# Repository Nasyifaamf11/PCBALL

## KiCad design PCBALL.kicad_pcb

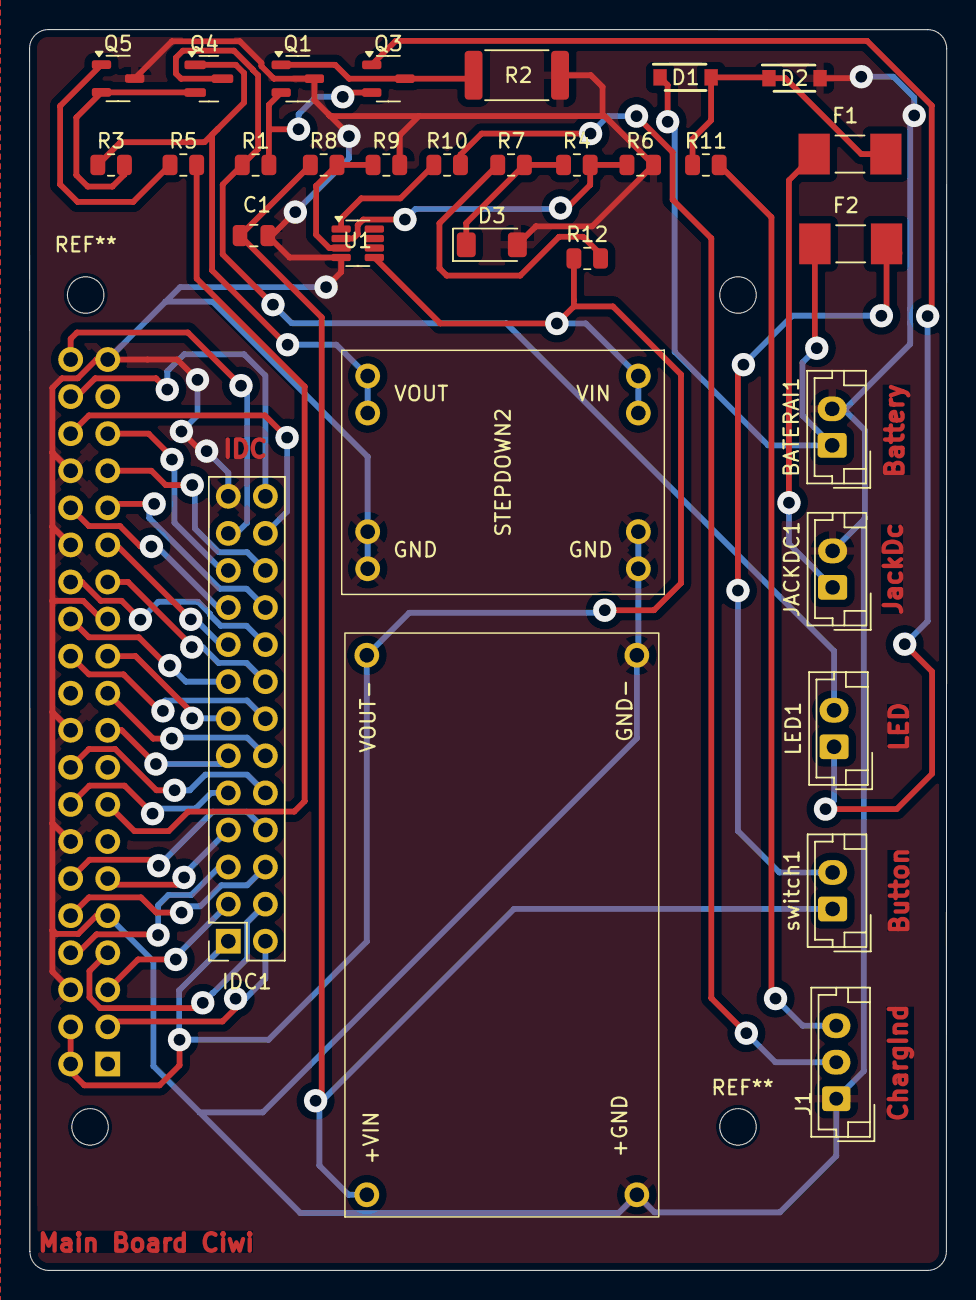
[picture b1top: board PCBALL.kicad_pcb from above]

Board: 2 copper layers, 62.8 x 85.0 mm, 32 parts (1 on the bottom side), 46 nets.

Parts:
BATERAI1: Conn_01x02_Pin; JST_EH_B2B-EH-A_1x02_P2.50mm_Vertical
C1: C; C_0805_2012Metric
D1: SS34; SODFL3818X130N
D2: 1N007; SODFL3818X130N
D3: D_Zener_Filled; D_MiniMELF
F1, F2: Fuse; FUSC6125X279N
IDC1: Conn_02x13_Odd_Even; PinSocket_2x13_P2.54mm_Vertical
J1: Conn_01x03_Pin; JST_EH_B3B-EH-A_1x03_P2.50mm_Vertical
JACKDC1: Conn_01x02_Pin; JST_EH_B2B-EH-A_1x02_P2.50mm_Vertical
LED1: Conn_01x02_Pin; JST_EH_B2B-EH-A_1x02_P2.50mm_Vertical
Q1, Q5: D882; SOT-23-3
Q3: Q_NMOS_DGS; SOT-23-3
Q4: MDD3752; SOT-23
R1: R; R_0805_2012Metric
R2: R; R_2512_6332Metric
R3: 10k; R_0805_2012Metric
R4, R6, R8, R9, R10: 10 K; R_0805_2012Metric
R5, R11: 1k; R_0805_2012Metric
R7, R12: 100; R_0805_2012Metric
Rapberry1: Conn_02x20_Odd_Even; PinSocket_2x20_P2.54mm_Vertical
STEPDOWN2: mp1584EN1
STEPUP2: TPS61088
U1: SOT-23-8
switch1: Conn_01x02_Pin; JST_EH_B2B-EH-A_1x02_P2.50mm_Vertical

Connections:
+3.3V: Q4.1 (D), R3.1, STEPDOWN2.3 (VOUT+)
+4.2V: C1.1, R8.1, STEPUP2.1 (VIN), switch1.1
+5V: IDC1.1, R12.1, Rapberry1.2, Rapberry1.4, STEPDOWN2.1 (VIN+), STEPUP2.3 (VOUT), U1.5 (V+)
Battery: BATERAI1.1, D1.1 (K), F2.1
Charg Ind: J1.3, R11.2
DATA0: IDC1.7, Rapberry1.11
DATA1: IDC1.8, Rapberry1.12
DATA2: IDC1.21, Rapberry1.35
DATA3: IDC1.26, Rapberry1.38
DATA4: IDC1.23, Rapberry1.40
DATA5: IDC1.11, Rapberry1.19
DATA6: IDC1.13, Rapberry1.23
DATA7: IDC1.19, Rapberry1.32
DATA8: IDC1.22, Rapberry1.33
DATA9: IDC1.5, Rapberry1.8
DATA10: IDC1.6, Rapberry1.10
DATA11: IDC1.17, Rapberry1.29
DATA12: IDC1.20, Rapberry1.31
DATA13: IDC1.15, Rapberry1.26
DATA14: IDC1.14, Rapberry1.24
DATA15: IDC1.12, Rapberry1.21
DATA16: IDC1.24, Rapberry1.36
DATA17: IDC1.4, Rapberry1.7
DATAEN: IDC1.18, Rapberry1.28
EXT_SCL: IDC1.10, Rapberry1.18
EXT_SDA: IDC1.9, Rapberry1.16
GND: BATERAI1.2, C1.2, D2.2 (A), D3.2 (A), IDC1.25, J1.1, JACKDC1.2, Q1.3 (C), Q5.3 (C), R2.2, R6.2, R9.2, Rapberry1.6, Rapberry1.9, Rapberry1.14, Rapberry1.20, Rapberry1.25, Rapberry1.30, Rapberry1.34, Rapberry1.39, STEPDOWN2.2 (VIN-), STEPDOWN2.4 (VOUT-), STEPUP2.2 (GND), STEPUP2.4 (GND), U1.4 (V-)
GPIO22: R5.2, Rapberry1.15
HSYNC: IDC1.3, Rapberry1.5
Low bat: J1.2, R10.2
unnamed: D1.2 (A), D2.1 (K), F1.2, R11.1
unnamed: D3.1 (K), R4.1, R7.2
unnamed: F1.1, JACKDC1.1
unnamed: LED1.1, Q3.1 (D)
unnamed: LED1.2, Q4.3 (S), R1.1
unnamed: Q1.1 (B), Q3.3 (S), R2.1
unnamed: Q1.2 (E), Q3.2 (G), R1.2
unnamed: Q4.2 (G), Q5.2 (E), R3.2
unnamed: Q5.1 (B), R5.1
unnamed: R10.1, U1.1
unnamed: R7.1, R12.2
unnamed: R8.2, R9.1, U1.3 (+)
unnamed: R4.2, R6.1, U1.2 (-)
unnamed: F2.2, switch1.2
PCLK: IDC1.16, Rapberry1.27
VSYNC: IDC1.2, Rapberry1.3

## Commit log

2025-09-16 3d fusion
2025-09-16 neww
2025-09-16 update schematic
2025-09-17 selesai nge routing jalur
